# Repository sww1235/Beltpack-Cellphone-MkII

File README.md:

# Beltpack-Cellphone-MkII
updated version of my original beltpack cellphone

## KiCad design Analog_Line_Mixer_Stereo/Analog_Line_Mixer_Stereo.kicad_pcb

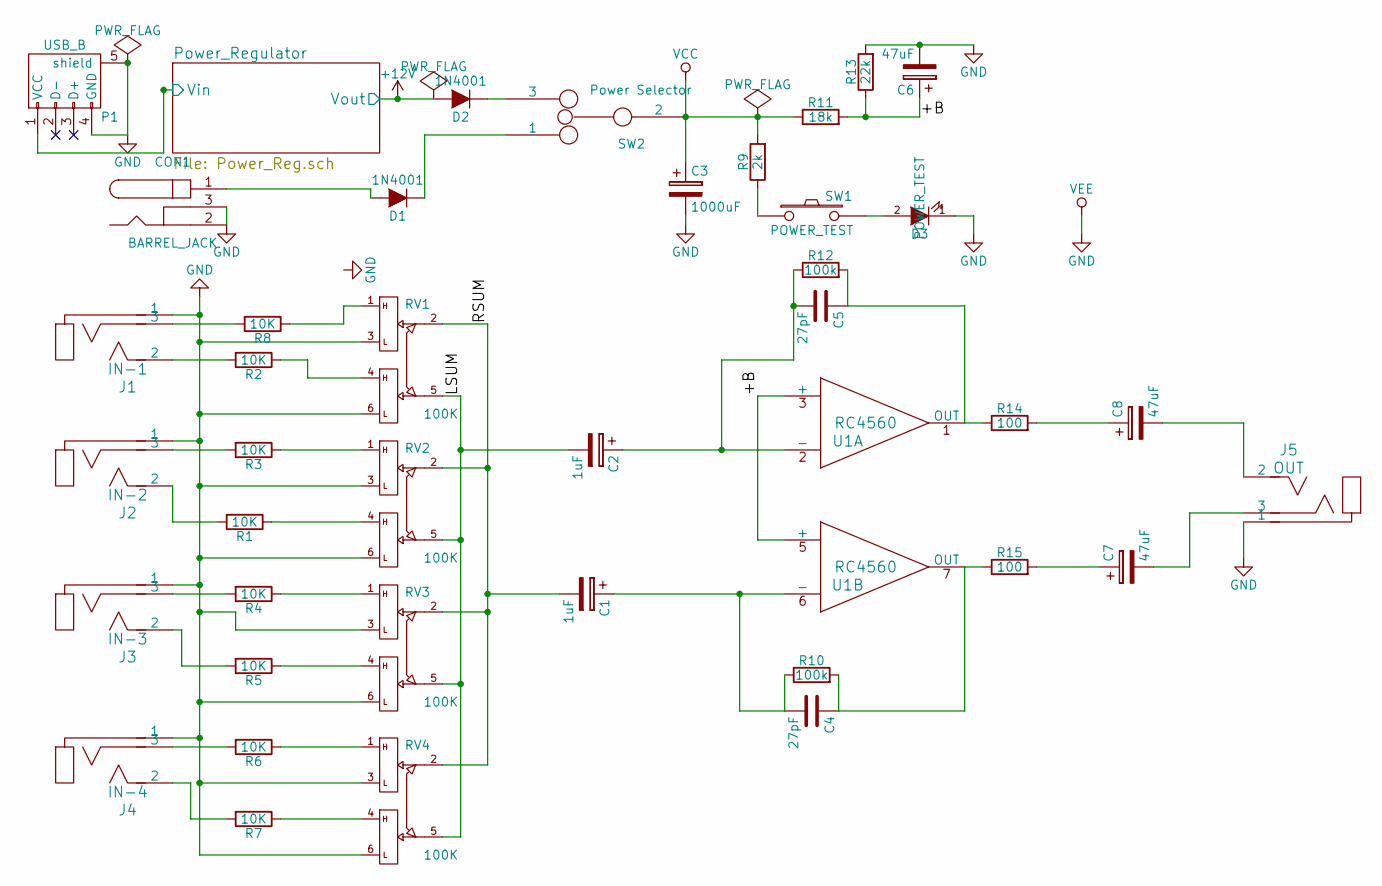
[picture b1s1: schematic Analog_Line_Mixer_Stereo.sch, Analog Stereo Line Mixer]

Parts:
C1, C2: 1uF; C_1206
C3: 1000uF; C_1206
C4, C5: 27pF; C_1206
C6, C7, C8: 47uF; C_1206
CON1: BARREL_JACK; Barrel_Jack_2.1x5.5mm_CUI_INC
D1, D2: 1N4001; SOD-323
D3: POWER_TEST; LED_0603
J1: IN-1; SJ1-353XNG-5Pin
J2: IN-2; SJ1-353XNG-5Pin
J3: IN-3; SJ1-353XNG-5Pin
J4: IN-4; SJ1-353XNG-5Pin
J5: OUT; SJ1-353XNG-5Pin
P1: USB_B; USB_Micro-B
R1, R2, R3, R4, R5, R6, R7, R8: 10K; R_1206
R9: 2k; R_1206
R10, R12: 100k; R_1206
R11: 18k; R_1206
R13: 22k; R_1206
R14, R15: 100; R_1206
RV1, RV2, RV3, RV4: 100K; TA-Dual-Pot-pin-RV122F
SW1: POWER_TEST; Grayhill-38F-M6-SPST
SW2: Power Selector; Grayhill-47B-switches-SPDT-M6
U1: RC4560; TI-LM2698-MUA08A

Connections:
+12V: D2.2 (A); also elsewhere on the board
/+B: C6.1, R11.2, R13.1, U1.3 (+), U1.5 (+)
/LSUM: C2.2, RV1.5, RV2.5, RV3.5, RV4.5
/Power_Regulator/Vin: P1.1 (VCC); also elsewhere on the board
/RSUM: C1.2, RV1.2, RV2.2, RV3.2, RV4.2
GND: C3.2, C6.2, CON1.2, CON1.3, D3.1 (K), J1.1, J2.1, J3.1, J4.1, J5.1, P1.4 (GND), P1.5 (shield), R13.2, RV1.3, RV1.6, RV2.3, RV2.6, RV3.3, RV3.6, RV4.3, RV4.6, U1.4 (VEE); also elsewhere on the board
unnamed: C1.1, C4.2, R10.1, U1.6 (-)
unnamed: C2.1, C5.2, R12.1, U1.2 (-)
unnamed: C4.1, R10.2, R15.1, U1.7 (OUT)
unnamed: C5.1, R12.2, R14.1, U1.1 (OUT)
unnamed: C7.1, R15.2
unnamed: C7.2, J5.3
unnamed: C8.1, R14.2
unnamed: C8.2, J5.2
unnamed: CON1.1, D1.2 (A)
unnamed: D1.1 (K), SW2.1
unnamed: D2.1 (K), SW2.3
unnamed: D3.2 (A), SW1.2
unnamed: J1.2, R2.2
unnamed: J1.3, R8.2
unnamed: J2.2, R1.2
unnamed: J2.3, R3.2
unnamed: J3.2, R5.2
unnamed: J3.3, R4.2
unnamed: J4.2, R7.2
unnamed: J4.3, R6.2
unnamed: R1.1, RV2.4
unnamed: R2.1, RV1.4
unnamed: R3.1, RV2.1
unnamed: R4.1, RV3.1
unnamed: R5.1, RV3.4
unnamed: R6.1, RV4.1
unnamed: R7.1, RV4.4
unnamed: R8.1, RV1.1
unnamed: R9.1, SW1.1
VCC: C3.1, R9.2, R11.1, SW2.2, U1.8 (VCC)

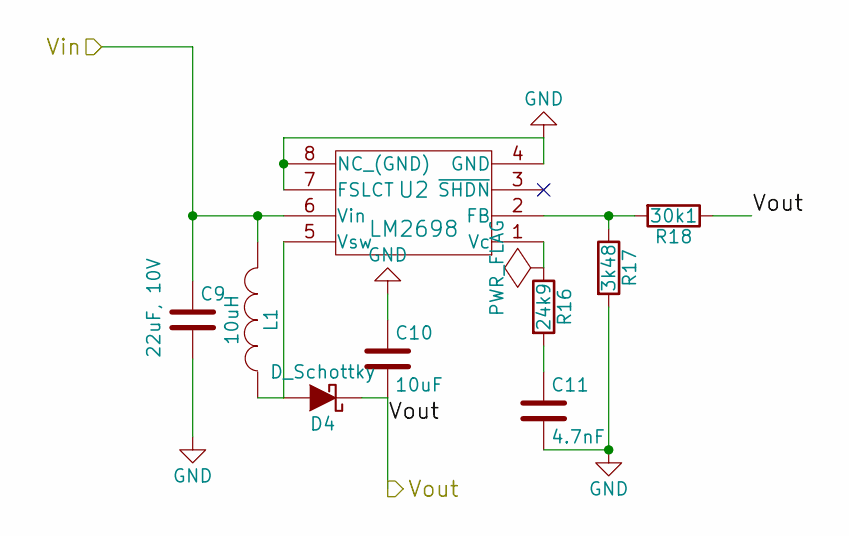
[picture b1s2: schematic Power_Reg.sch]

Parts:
C9: 22uF, 10V; C_1206
C10: 10uF; C_1206
C11: 4.7nF; C_1206
D4: D_Schottky; SOD-123
L1: 10uH; R_0805
R16: 24k9; R_1206
R17: 3k48; R_1206
R18: 30k1; R_1206
U2: LM2698; TI-LM2698-MUA08A

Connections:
+12V: C10.2, D4.1 (K), R18.1; also elsewhere on the board
/Power_Regulator/Vin: C9.1, L1.2, U2.6 (Vin); also elsewhere on the board
GND: C9.2, C10.1, C11.2, R17.2, U2.4 (GND), U2.7 (FSLCT), U2.8 (NC_(GND)); also elsewhere on the board
unnamed: C11.1, R16.2
unnamed: D4.2 (A), L1.1, U2.5 (Vsw)
unnamed: R16.1, U2.1 (Vc)
unnamed: R17.1, R18.2, U2.2 (FB)

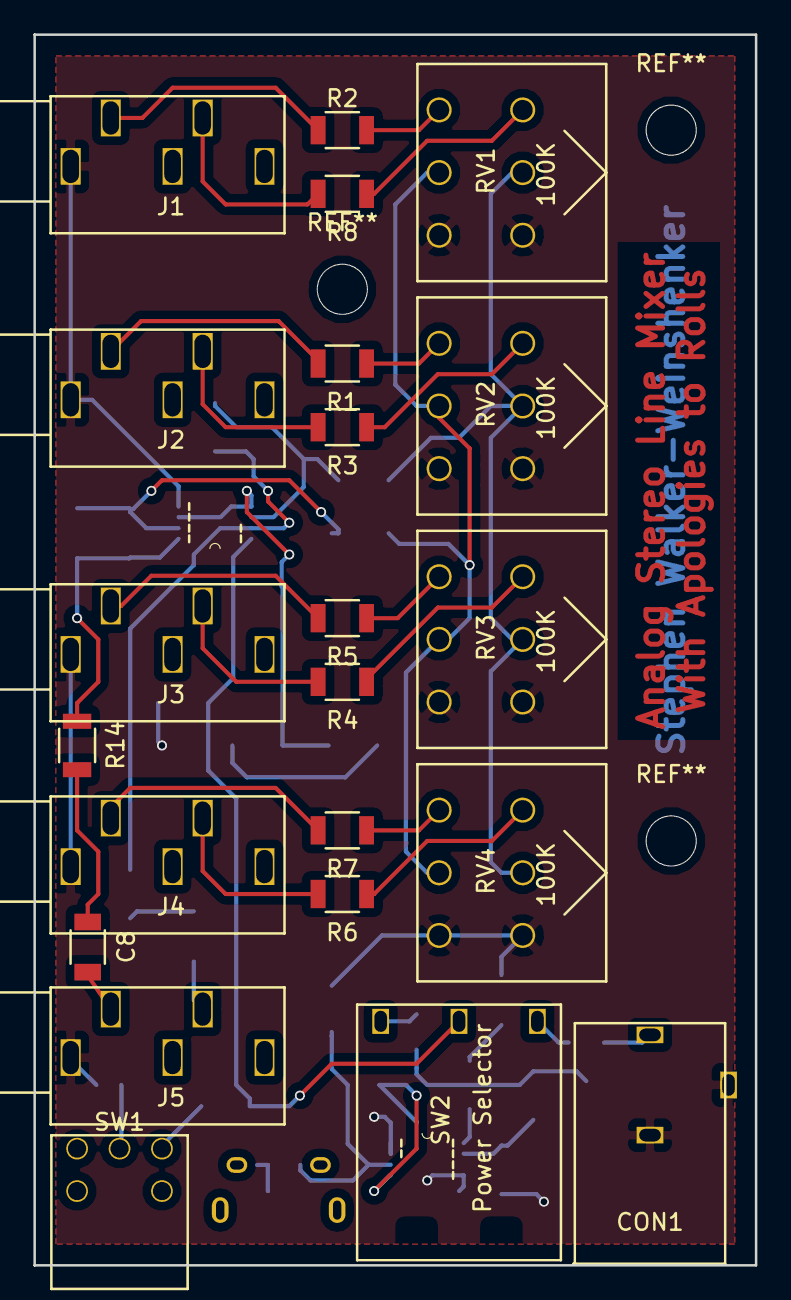
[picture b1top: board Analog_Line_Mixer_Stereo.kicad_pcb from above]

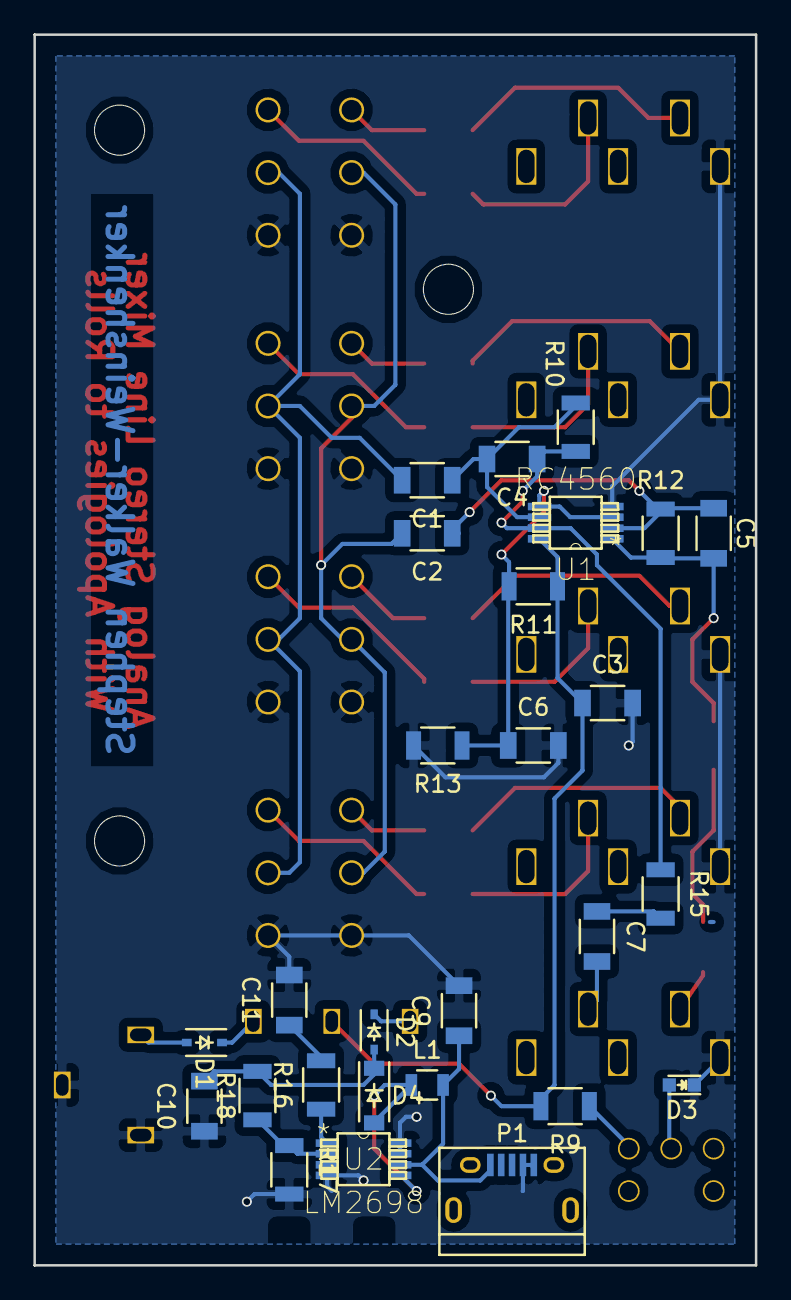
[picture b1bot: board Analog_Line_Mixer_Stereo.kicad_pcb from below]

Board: 2 copper layers, 43.2 x 73.7 mm, 49 parts (27 on the bottom side), 40 nets.

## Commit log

2015-10-31 Create idea file
2015-10-31 Update idea file
2016-01-29 change to markdown format
2016-01-29 Testing links
2016-01-29 testing links again
2016-01-31 adding circuit board kicad projects
2016-02-04 adding analog mixer schematic
2016-02-04 fixing title blocks and sheet sizes
2016-02-04 final commit for the night
2016-02-08 adding switches and power sources
2016-02-08 finalized schematic and started on board
2016-02-09 mostly finalized component placement, starting routing
2016-02-09 routing mostly finished, need to check TSSOP package and other packages for soldermask specs
2016-02-09 adding footprints and dimensions
2016-02-09 removing _saved_ file that was deleted by kicad
2016-02-09 creating gerbers
2016-02-09 creating .gitignore
2016-02-09 modifiying gerbers
